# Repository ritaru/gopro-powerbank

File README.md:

## 5V 3A Capable Single 18650 Power Bank

The required components are as follows.

Parts are 2.0*1.2mm (2012 metric) if there is no further notation.

| Schematic Number | Value | Notes |
|:---:|:---:|:---:|
| BT1 / BT2 | Generic 18650 Holder | SMD / Through-Hole capable |
| U1 | TPS61022RWUR | Texas Instruments has the only capable IC |
| U2 | TP4056 | Generic TP4056 will work |
| U3 | S-8261 | DW01A also work |
| U4 | 8205A | Generic ones work |
| U5 | 8205A | Generic ones work |
| J1 | USB-C Receptacle | HRO Type, Recommending LCSC #C2765186 |
| R1 | 732k | Based on TPS61022 datasheet |
| R2 | 100k | Based on TPS61022 datasheet |
| R3 | 1.2k | Based on TP4056 datasheet |
| R4 | 1k | Based on TP4056 datasheet, decrease if not bright enough |
| R5 | 1k | Based on TP4056 datasheet, decrease if not bright enough |
| R6 | 1k | Based on DW01A datasheet, change if S-8261 is used |
| R7 | 100 | Based on DW01A datasheet, change if S-8261 is used |
| R8 | 5.1k | USB-C CC pin pull down |
| R9 | 5.1k | USB-C CC pin pull down |
| C1 | 10u / 10V | X5R, MLCC |
| C2 | 10u / 10V | X5R, MLCC |
| C3 | 0.1u / 50V | MLCC |
| C4 | 22u / 10V | X5R, MLCC |
| C5 | 22u / 10V | X5R, MLCC |
| C6 | 22u / 10V | X5R, MLCC |
| C7 | 0.1u / 50V | MLCC |
| C8 | 0.1u / 50V | MLCC |
| L1 | 1u | XAL7030-102MEC, TI reference design |
| D1 | Generic LED | STANDBY |
| D2 | Generic LED | CHARGING |
| D3 | TVS Diode | 5.6V Breakdown, SOD-323 |

## Side notes

- This is designed for Gopro Hero 9/10/11/12.
- Gopro Hero 9/10/11/12 requires a charger that is capable of delivering more than 10W(5V 2A) with no internal battery.
- I find this design to be also suitable for outdoor use when appropriate enclosure is added for a helmet mount.
- For copper weight on the PCB, it is 2oz minimum. (Due to limitation of L1 contacts on TPS61022)
- It automatically engages PFM(Pulse Frequency Modulation) when on low load. The MODE pin is pulled down.
- When not in use, please disconnect the battery. There is no onboard switch for on/off feature. (I might add this though)
- TP4056 happens to be quite hot when charging. Use separate charging tools (such as XTAR or Nitecore) for durability.
- I haven't built this yet, so additional features may be added later.

### AGPL v3.0 License
This repository is using AGPL v3.0.

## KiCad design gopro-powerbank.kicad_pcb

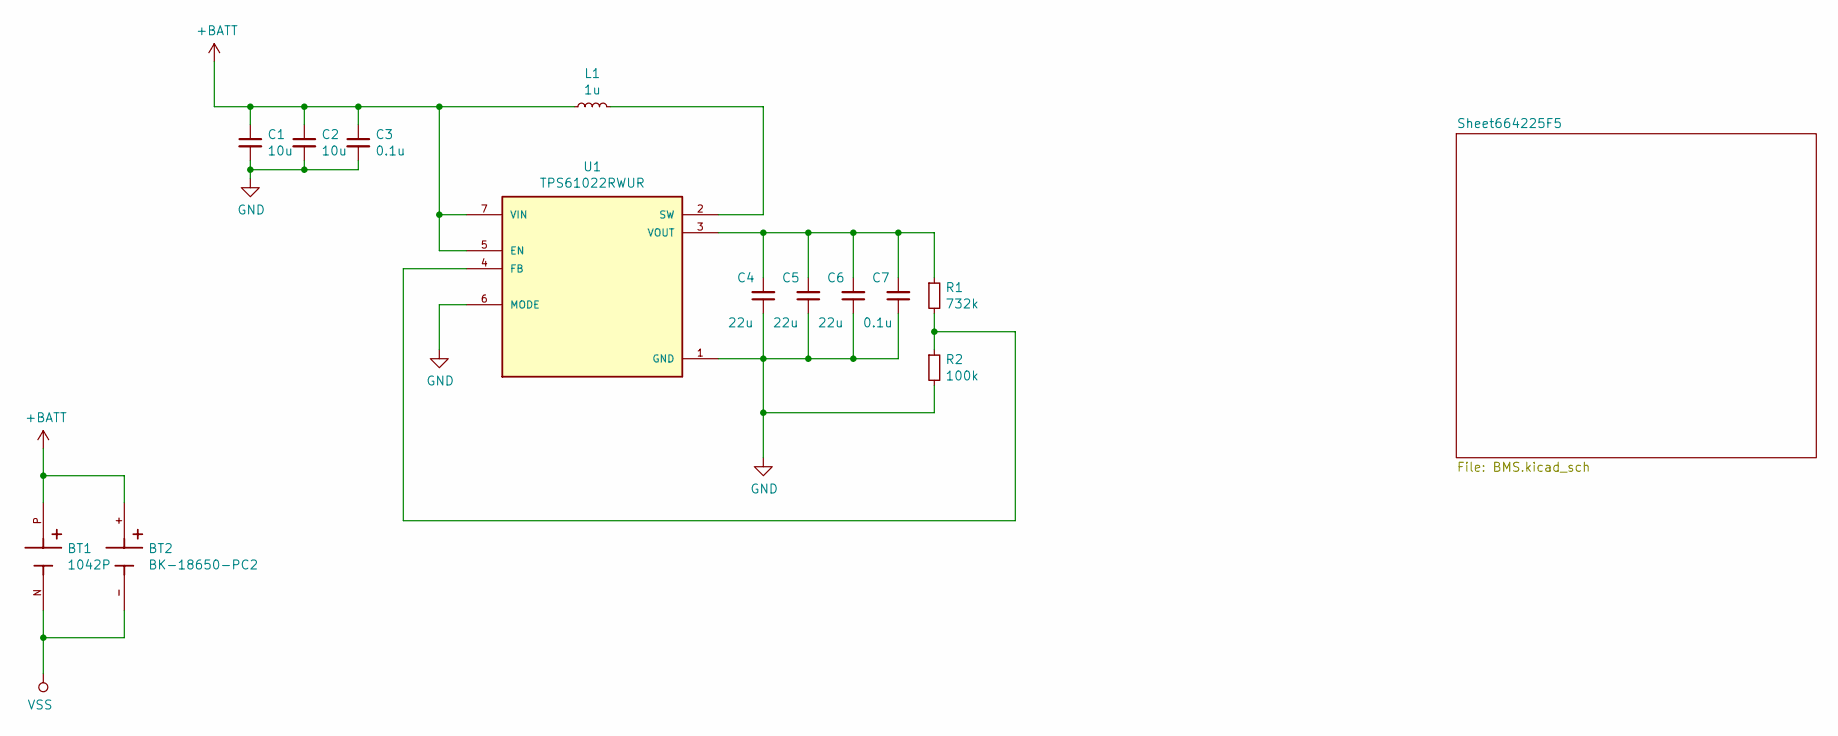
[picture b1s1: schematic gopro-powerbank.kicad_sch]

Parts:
BT1: 1042P; BAT_1042P; PARTREV E
BT2: BK-18650-PC2; BAT_BK-18650-PC2; PARTREV F
C1, C2: 10u; C_0805_2012Metric_Pad1.15x1.40mm_HandSolder
C3, C7: 0.1u; C_0805_2012Metric_Pad1.15x1.40mm_HandSolder
C4, C5, C6: 22u; C_0805_2012Metric_Pad1.15x1.40mm_HandSolder
L1: 1u; INDDFN750X750X310-2N
R1: 732k; R_0805_2012Metric_Pad1.15x1.40mm_HandSolder
R2: 100k; R_0805_2012Metric_Pad1.15x1.40mm_HandSolder
U1: TPS61022RWUR; CONV_TPS61022RWUR; PARTREV 4223724/C 02/2018

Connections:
+BATT: BT1.P, BT2.+, C1.1, C2.1, C3.1, L1.1, U1.5 (EN), U1.7 (VIN); also elsewhere on the board
GND: C1.2, C2.2, C3.2, C4.1, C5.1, C6.1, C7.1, R2.2, U1.1 (GND), U1.6 (MODE); also elsewhere on the board
unnamed: C4.2, C5.2, C6.2, C7.2, R1.1, U1.3 (VOUT)
unnamed: L1.2, U1.2 (SW)
unnamed: R1.2, R2.1, U1.4 (FB)
VSS: BT1.N, BT2.-; also elsewhere on the board

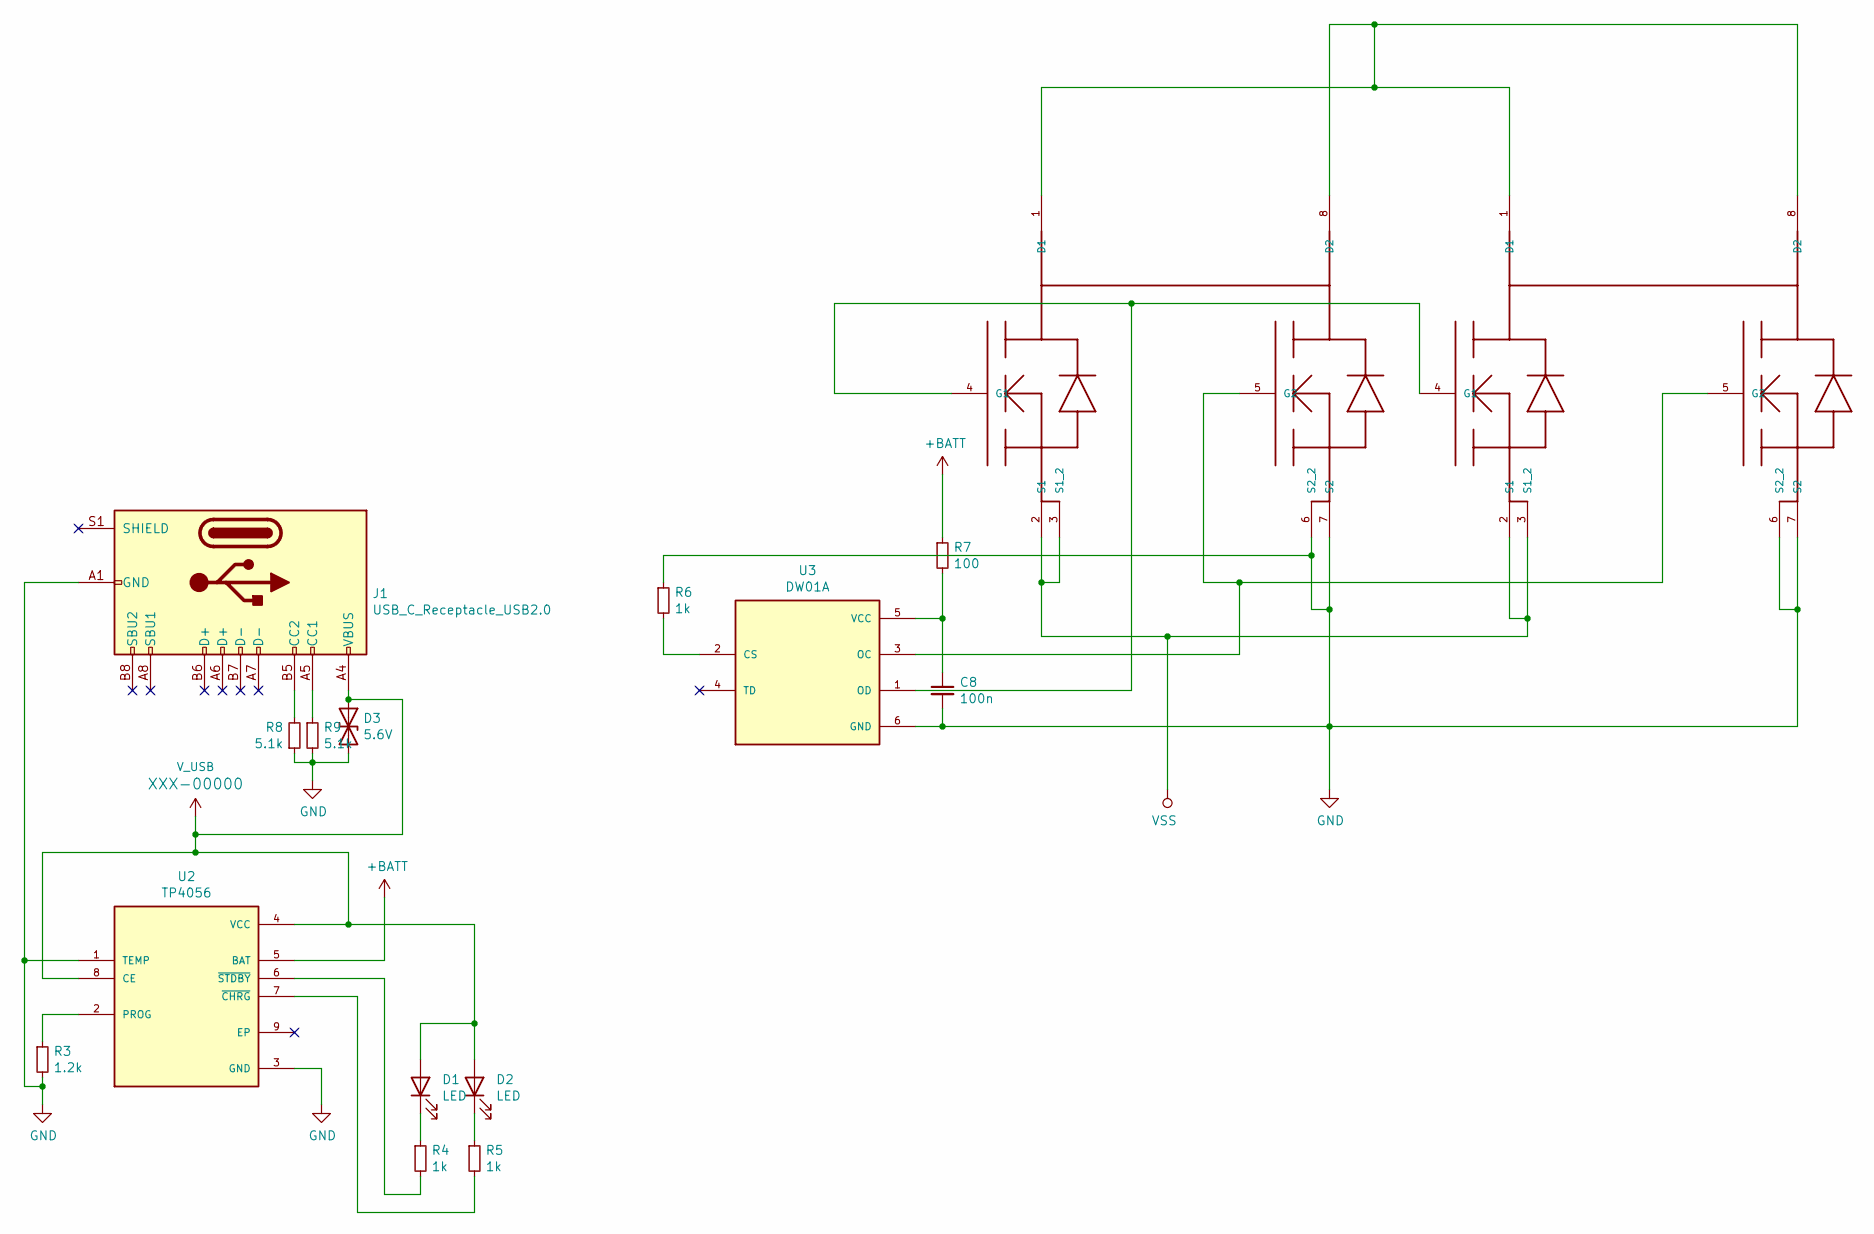
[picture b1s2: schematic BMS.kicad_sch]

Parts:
C8: 100n; C_0805_2012Metric_Pad1.15x1.40mm_HandSolder
D1, D2: LED; LED_0805_2012Metric_Pad1.15x1.40mm_HandSolder
D3: 5.6V; D_SOD-323_HandSoldering
J1: USB_C_Receptacle_USB2.0; USB_C_Receptacle_HRO_TYPE-C-31-M-12
R3: 1.2k; R_0805_2012Metric_Pad1.15x1.40mm_HandSolder
R4, R5, R6: 1k; R_0805_2012Metric_Pad1.15x1.40mm_HandSolder
R7: 100; R_0805_2012Metric_Pad1.15x1.40mm_HandSolder
R8, R9: 5.1k; R_0805_2012Metric_Pad1.15x1.40mm_HandSolder
U2: TP4056; SOP127P600X175-9N
U3: DW01A; SOT95P280X145-6N; PARTREV 1.8
U4, U5: 8205A; TSSOP8

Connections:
+BATT: R7.1, U2.5 (BAT); also elsewhere on the board
GND: C8.2, D3.2 (A2), J1.A1 (GND), J1.A12 (GND), J1.B1 (GND), J1.B12 (GND), R3.2, R6.1, R8.1, R9.2, U2.1 (TEMP), U2.3 (GND), U3.6 (GND), U4.6 (S2_2), U4.7 (S2), U5.6 (S2_2), U5.7 (S2); also elsewhere on the board
unnamed: C8.1, R7.2, U3.5 (VCC)
unnamed: D1.1 (K), R4.1
unnamed: D2.1 (K), R5.1
unnamed: J1.A5 (CC1), R9.1
unnamed: J1.B5 (CC2), R8.2
unnamed: R3.1, U2.2 (PROG)
unnamed: R4.2, U2.6 (~STDBY)
unnamed: R5.2, U2.7 (~CHRG)
unnamed: R6.2, U3.2 (CS)
unnamed: U3.1 (OD), U4.4 (G1), U5.4 (G1)
unnamed: U3.3 (OC), U4.5 (G2), U5.5 (G2)
unnamed: U4.1 (D1), U4.8 (D2), U5.1 (D1), U5.8 (D2)
VSS: U4.2 (S1), U4.3 (S1_2), U5.2 (S1), U5.3 (S1_2); also elsewhere on the board
V_USB: D1.2 (A), D2.2 (A), D3.1 (A1), J1.A4 (VBUS), J1.A9 (VBUS), J1.B4 (VBUS), J1.B9 (VBUS), U2.4 (VCC), U2.8 (CE)

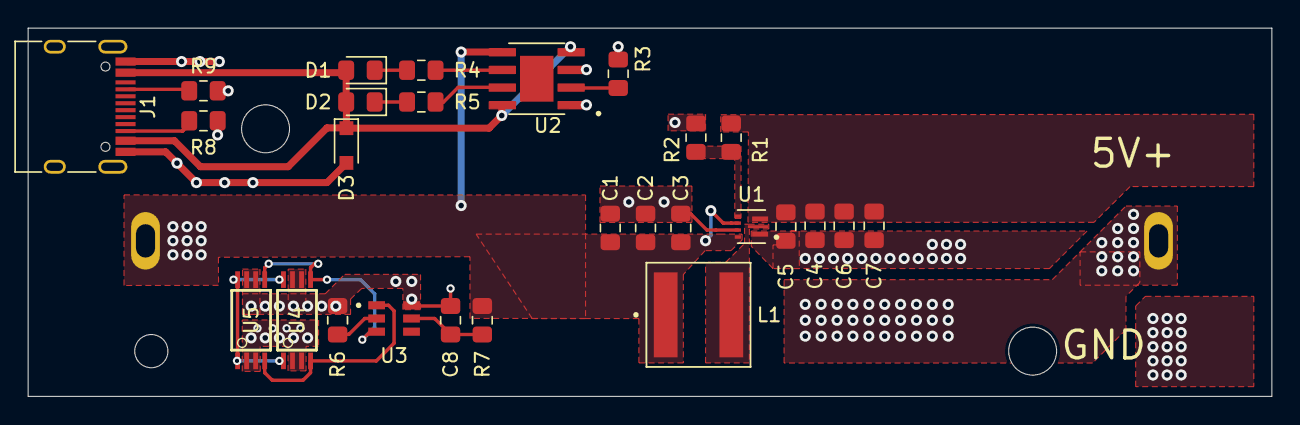
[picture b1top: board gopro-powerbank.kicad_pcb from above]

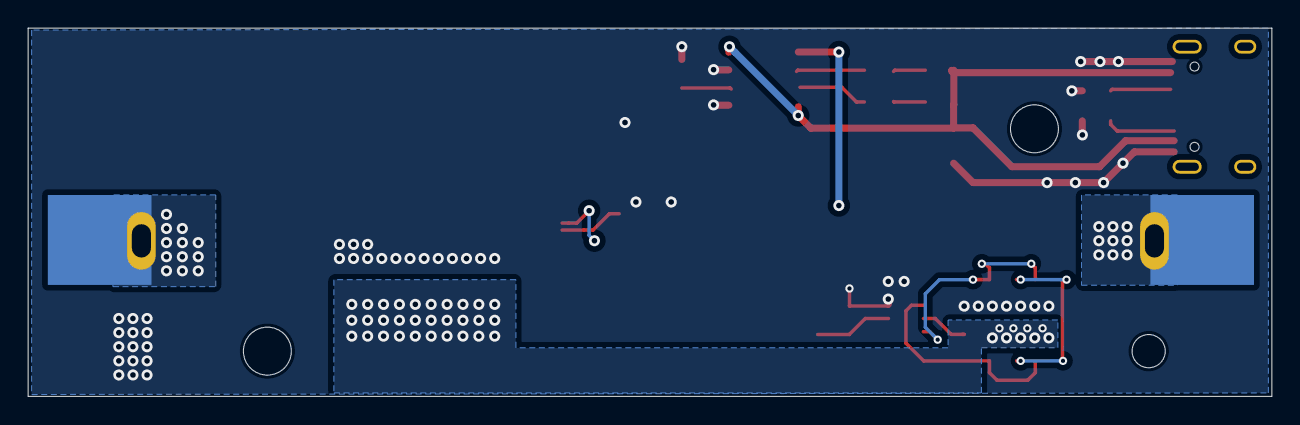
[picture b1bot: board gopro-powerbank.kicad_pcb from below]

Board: 2 copper layers, 89.5 x 26.5 mm, 29 parts (2 on the bottom side), 19 nets.

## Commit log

2024-05-13 added readme
2024-05-13 Added AGPL License
2025-03-06 added library and footprints
2025-03-06 kicad version upgrade
2025-03-06 rescue symbols
